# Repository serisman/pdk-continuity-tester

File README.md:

# pdk-continuity-tester
A simple standalone continuity tester, based on the ultra-inexpensive (~$0.03) Padauk microcontroller and a piezo buzzer.
- Turns on a Piezo Buzzer when there is continuity detected between the Probe pin and GND.
- Uses the Comparator to test for continuity (i.e. Reference(+) > Probe(-)).
- Goes to sleep after a short duration of inactivity to save battery power (< 0.5 uA).
- Optional LED indicates device is powered on and not sleeping.

This is a port of, and based on an original project for the ATtiny85(V) by David Johnson-Davies:
- http://www.technoblogy.com/show?1YON
- https://github.com/technoblogy/continuity-tester

### Links
- [Firmware](firmware/)
- [PCB](pcb-s08/)

### Hardware Circuit

##### Schematic
(for 8-pin PFS154, PFS173, PMS150C/PMS15A, PMS152, PMS154C, PMS171B)

**Probe/Reference**:

One lead of the Probe is connected to one of the Comparator (-) pins, and the other lead is connected to GND. 
- The Probe lead is placed on the PA3 pin (Port A, Bit 3).

The Reference uses the Comparator (+) pin, with a 47 ohm resistor to GND.
- The Reference is placed on the PA4 pin (Port A, Bit 4). 

**Buzzer**:

The Buzzer is placed on the PA5 pin (Port A, Bit 5).  It is also connected to the PA6 pin, but the current firmware doesn't use this (yet).

For devices with an 11-bit PWM (i.e. PFS154, PFS173, PMS152, PMS154C), PA5 is also one of the PWM pins, enabling PWM control of the Buzzer's frequency using a Passive buzzer.

For other devices (i.e. PMS150C/PMS15A, PMS171B), the Buzzer can only be turned on/off and an Active buzzer is required.

In either case the Buzzer is used with a current sink configuration.

This means that one side of the Buzzer is connected to VDD, and the other is connected (through a current limiting resistor) to the digital pin of the IC.
- To enable the Buzzer (Passive / PWM), it is driven with an inverted 50% duty cycle at approx 2kHz.
- To enable the Buzzer (Active), it is driven LOW, meaning current will flow.
- To disable the Buzzer, it is floated HIGH, meaning no current will flow.

**LED**:

The LED is placed on the PA7 pin (Port A, Bit 7) with a current sink configuration.

This means the negative leg (or cathode) of the LED is connected to the digital pin of the IC, and the positive leg (or anode) of the LED is connected through a current limiting resistor to VDD.
- When the digital pin is LOW, current will flow through the LED and it will light up.
- When the digital pin is HIGH, no current will flow and the LED will turn off.

### Compatibility
This project is currently intended to be run (without modifications) on the PFS154, PFS173, PMS150C/PMS15A, PMS152, PMS154C, and PMS171B Padauk microcontrollers,
but it should be able to be modified to run on just about every currently known Padauk microcontroller that is supported by SDCC and the Easy PDK Programmer.
Some microcontrollers will require additional definitions in the [firmware/hal.h](firmware/hal.h) file,
and less common devices may require additional device specific include files (firmware/pdk/device/*.h) to be supplied.

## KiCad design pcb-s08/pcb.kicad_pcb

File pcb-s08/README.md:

# pcb-s08 ([pdk-continuity-tester](https://github.com/serisman/pdk-continuity-tester/))

### Schematic
(for 8-pin PFS154, PFS173, PMS150C, PMS15A, PMS152, PMS154C, PMS171B)

### PCB

This PCB design was created with KiCad, and has been [shared on OSHPARK](https://oshpark.com/shared_projects/1CFwpMAd).
There are also gerber files available in the [output/gerber/](output/gerber/) directory, or [gerber.zip](output/gerber.zip).

Attach a ~12mm Piezo Buzzer to the end. PMS150C, PMS15A, and PMS171B require an Active (on/off) buzzer.  PFS154, PFS173, PMS152, and PMS154C use a Passive (PWM) buzzer.

Attach a CR1225 (or CR1220, CR1025, CR927, etc...) to the bottom after soldering a wire to hold it (and act as the positive contact).

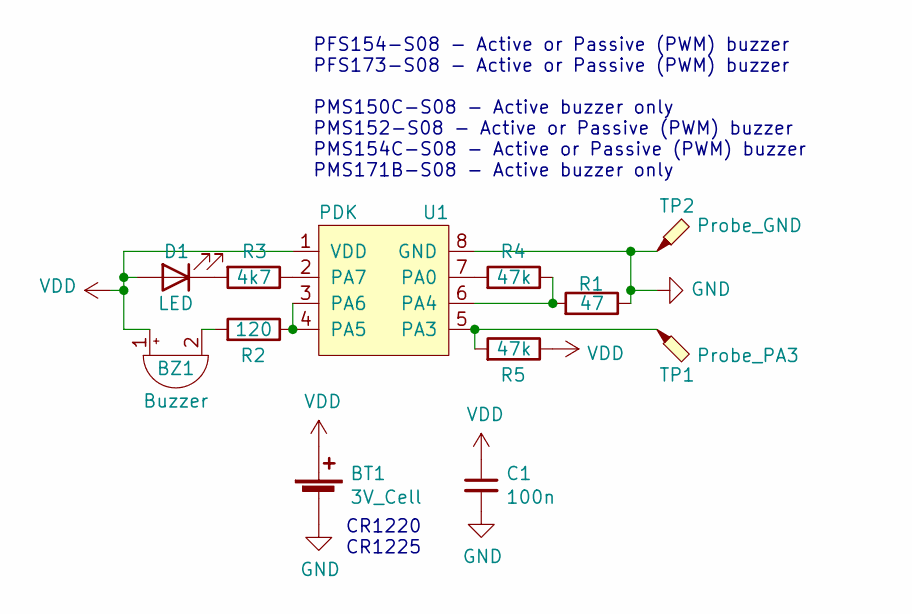
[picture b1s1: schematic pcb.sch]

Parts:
BT1: 3V_Cell; BatteryHolder_12mm
BZ1: Buzzer; Buzzer_12x9.5RM7.6
C1: 100n; C_0603
D1: LED; LED_0805
R1: 47; R_0603
R2: 120; R_0805
R3: 4k7; R_0603
R4, R5: 47k; R_0603
TP1: Probe_PA3; Pad_2.0x3.0mm
TP2: Probe_GND; Pad_2.0x3.0mm
U1: PDK; SOP-8_3.9x4.9mm_P1.27mm

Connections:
GND: BT1.2 (-), C1.2, R1.1, TP2.1, U1.8 (GND)
unnamed: BZ1.2 (+), R2.2
unnamed: D1.1 (K), R3.2
unnamed: R1.2, R4.1, U1.6 (PA4)
unnamed: R2.1, U1.3 (PA6), U1.4 (PA5)
unnamed: R3.1, U1.2 (PA7)
unnamed: R4.2, U1.7 (PA0)
unnamed: R5.2, TP1.1, U1.5 (PA3)
VDD: BT1.1 (+), BZ1.1 (-), C1.1, D1.2 (A), R5.1, U1.1 (VDD)

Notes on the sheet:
PFS154-S08 - Active or Passive (PWM) buzzer PFS173-S08 - Active or Passive (PWM) buzzer PMS150C-S08 - Active buzzer only PMS152-S08 - Active or Passive (PWM) buzzer PMS154C-S08 - Active or Passive (PWM) buzzer PMS171B-S08 - Active buzzer only
CR1220 CR1225

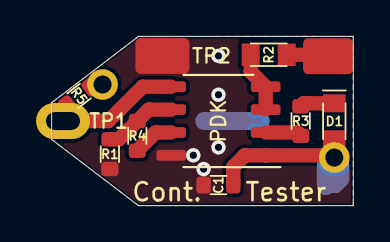
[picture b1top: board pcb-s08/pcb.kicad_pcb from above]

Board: 2 copper layers, 16.8 x 9.4 mm, 12 parts (1 on the bottom side), 9 nets.

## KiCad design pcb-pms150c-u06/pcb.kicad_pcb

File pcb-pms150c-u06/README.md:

# pcb-pms150c-u06 ([pdk-continuity-tester](https://github.com/serisman/pdk-continuity-tester/))

### Schematic for 6-pin PMS150C/PMS15A
> 

### PCB

This PCB design was created with KiCad, and has been [shared on OSHPARK](https://oshpark.com/shared_projects/XcWQiX7z).
There are also gerber files available in the [output/gerber/](output/gerber/) directory.
This design is meant to be attached to the bottom of a ~12mm Piezo Buzzer, where the SMD parts are first soldered to the board, and are underneath the buzzer.
There are through-holes for the two probe connections, and pads on the back for the battery connections.
2x LR44 battery cells in series would pair nicely with this PCB, as they are a good voltage match, and are approximately the same diameter
(meaning the whole thing can be heat shrunk together for a miniature continuity tester).

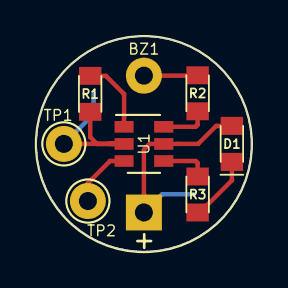
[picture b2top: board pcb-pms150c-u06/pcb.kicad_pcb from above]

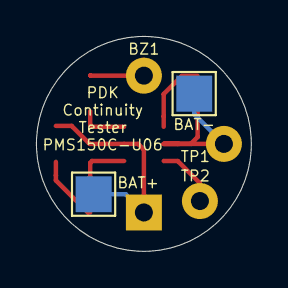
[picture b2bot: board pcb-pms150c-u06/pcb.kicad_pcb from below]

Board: 2 copper layers, 11.9 x 11.9 mm, 10 parts (2 on the bottom side), 8 nets.

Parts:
BZ1: Buzzer; Buzzer_12x9.5RM7.6
D1: LED; LED_0805
J1: BAT-; TestPoint_Pad_2.0x2.0mm
J2: BAT+; TestPoint_Pad_2.0x2.0mm
R1: 47; R_0805
R2: 120; R_0805
R3: 4k7; R_0805
TP1: Probe_GND; TestPoint_THTPad_D2.0mm_Drill1.0mm
TP2: Probe_PA6; TestPoint_THTPad_D2.0mm_Drill1.0mm
U1: PMS150C-U06; SOT-23-6

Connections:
GND: J1.1, R1.2, TP1.1, U1.2
unnamed: BZ1.2, R2.1
unnamed: D1.1, R3.1
unnamed: R1.1, U1.1
unnamed: R2.2, U1.6
unnamed: R3.2, U1.4
unnamed: TP2.1, U1.3
VDD: BZ1.1, D1.2, J2.1, U1.5

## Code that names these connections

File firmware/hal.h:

/*
  hal.h - Device specific definitions and helper methods for the pdk-continuity-tester project.

  ----------------------------------------------------------------------
  Copyright (C) 2020  serisman  <github@serisman.com>

  CC BY 4.0
  Licensed under a Creative Commons Attribution 4.0 International license:
  http://creativecommons.org/licenses/by/4.0/
*/

#ifndef __HAL_H__
#define __HAL_H__

#if !defined(PFS154) && !defined(PFS173) && !defined(PMS150C) && !defined(PMS15A) && !defined(PMS152) && !defined(PMS154C) && !defined(PMS171B)
  #error "Device not currently supported!"
#endif

// Define which pins to use
#define PULL_REF_HI_BIT   0     // 47k Reference pull-up resistor is on PA0 (Port A, Bit 0)
#define REFERENCE_BIT     4     // Reference is on PA4 (Port A, Bit 4), which is also Comp+
#define PROBE_BIT         3     // Probe is on PA3 (Port A, Bit 3), which is also Comp-
#define BUZZER_BIT        5     // Buzzer is placed on the PA5 pin (Port A, Bit 5), which is also PWM2 (Note: PWM not available on PMS150C,PMS15A,PMS171B)
//#define BUZZER_BIT      6     // Buzzer is placed on the PA6 pin (Port A, Bit 6)
#define LED_BIT           7     // LED is placed on the PA7 pin (Port A, Bit 7)

#define COMP_MINUS        GPCC_COMP_MINUS_PA3

// Helpers to initialize Buzzer PWM and turn Buzzer on/off
#if defined(PMS150C) || defined(PMS15A) || defined(PMS171B)
  inline void buzzerInitPWM() { }
  #define buzzerOn()          PA &= ~(1 << BUZZER_BIT)
  #define buzzerOff()         PA |= (1 << BUZZER_BIT)
  #warning Remember to use an Active Buzzer with PMS150C,PMS15A,PMS171B
#else
  #if defined(PWMG2CUBL)            // Full 11-bit PWM:   PFS154,PMS154C
    inline void buzzerInitPWM() {
      PWMG2CUBL = 0xC0;             // Set the PWM upper bound (255+1)
      PWMG2CUBH = 0x3F;
      PWMG2DTL = 0xE0;              // Set the PWM duty value (127 + 0.5 + 0.5) = 50%
      PWMG2DTH = 0x1F;
      PWMG2S = (uint8_t)(PWMG2S_SCALE_DIV32); // Set the PWM frequency to ~1.953 kHz
    }
    #define buzzerOn()          PWMG2C = (uint8_t)(PWMG2C_ENABLE | PWMG2C_INVERT_OUT | PWMG2C_OUT_PA5 | PWMG2C_CLK_IHRC)
    #define buzzerOff()         PWMG2C = 0x00; PA |= (1 << BUZZER_BIT)
  #elif defined(PWMGCUBL)           // Basic 11-bit PWM:  PFS173,PMS152
    inline void buzzerInitPWM() {
      PWMGCUBL = 0xC0;              // Set the PWM upper bound (255+1)
      PWMGCUBH = 0x3F;
      PWMG2DTL = 0xE0;              // Set the PWM duty value (127 + 0.5 + 0.5) = 50%
      PWMG2DTH = 0x1F;
      PWMGCLK = (uint8_t)(PWMGCLK_PWMG_ENABLE | PWMGCLK_CLK_IHRC | PWMGCLK_PRESCALE_DIV32); // Set the PWM frequency to ~1.953 kHz
    }
    #define buzzerOn()          PWMG2C = (uint8_t)(PWMG2C_INVERT_OUT | PWMG2C_OUT_PWMG2 | PWMG2C_OUT_PA5)
    #define buzzerOff()         PWMG2C = 0x00; PA |= (1 << BUZZER_BIT)
  #endif
#endif

// LED is active low (current sink), so define helpers for better readability
#define ledOn()             PA &= ~(1 << LED_BIT)
#define ledOff()            PA |= (1 << LED_BIT)

#endif //__HAL_H__

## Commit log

2020-07-16 Initial Version
2020-07-16 Add schematic for PMS150C-U06
2020-07-16 Add PCB for PMS150C-U06
2020-07-16 typo
2020-07-16 Update Schematic
2020-07-16 Rename pcb files
2020-07-16 Add Schematic for 8-pin PFS154, PFS173, PMS152, PMS154C
2020-07-16 Add additional ICs
2020-07-16 Add more ICs, add package information
2020-07-16 Add Package
2020-07-17 Move firmware to sub-directory
2020-07-17 Move PCB section out of main README and into sub-folder's README
2020-07-17 Fix typo related to PMS150C
2020-07-17 Fix typo in a comment
2020-07-17 Fix PWM code
2020-07-17 Don't set PADIER until right before going to sleep
2020-07-19 Use internal V ref instead of external resistor divider.
2020-07-19 Pull in upstream fixes
2020-07-21 Update Schematics
2022-12-21 Move some images around
2022-12-21 New version (using 8-pin IC with external pull-up resistors).
2022-12-21 Tweak README.md
2022-12-21 add erase
